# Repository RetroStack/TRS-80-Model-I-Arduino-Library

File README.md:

# TRS-80 Model I Arduino Library

**NOTE**: This library is under active development and breaking changes still happen between major versions. See the [changelog](CHANGELOG.md) for what changed in the current release, including the migration notes for 2.0.0.

Arduino library for interfacing with TRS-80 Model I hardware via the 40-pin edge connector. Control memory, video, keyboard, and bus signals to create ROM dumpers, RAM testers, and custom peripherals.

**Hardware Required:** Arduino Mega 2560 (only board with sufficient GPIO pins)

## Quick Start

### Basic Usage

```cpp
#include <M1Shield.h>
#include <Display_ST7789_320x240.h>  // Choose your display

Display_ST7789_320x240 displayProvider;

void setup() {
    M1Shield.begin(displayProvider);
}

void loop() {
    M1Shield.loop();
}
```

### Read & Write

```cpp
#include <Model1.h>

void setup() {
    Model1.begin();
    Model1.activateTestSignal();

    uint8_t data = Model1.readMemory(0x0000);  // Read ROM
    Model1.writeMemory(0x3C00, 0x41);          // Write to video RAM

    Model1.deactivateTestSignal();
}
```

### UI Framework with String Support

```cpp
#include <ContentScreen.h>

class MyScreen : public ContentScreen {
public:
    MyScreen() {
        // Three ways to set titles/text - choose what fits your needs:
        setTitle("Static Title");                    // Simple C-string
        setTitle(String("Score: ") + String(score)); // Dynamic Arduino String
        setTitleF(F("Memory Efficient"));            // Flash string (F-macro)
    }

protected:
    void _drawContent() override {
        // Draw dynamic content easily
        String playerName = "Alice";
        drawText(10, 10, String("Player: ") + playerName, WHITE);
        drawTextF(10, 30, F("Static text"), YELLOW);  // Saves RAM
    }
};
```

## Key Features

- **Complete TRS-80 Bus Control** - Read/write memory, control signals, interrupts
- **High-Level Classes** - Model1, Video, Keyboard, ROM, Cassette for easy access
- **Low-Level Access** - Model1LowLevel for advanced users requiring precise control
- **M1Shield Support** - Hardware abstraction for Arduino shield with display/input
- **UI Framework** - Screen management system for building interactive applications
- **Flexible String Support** - All text functions support C-strings, Arduino Strings, and F-strings
- **Multiple Display Support** - ST7789, ILI9341, ST7796, SSD1306, and more
- **Arduino Compatible** - Standard Print interface, familiar patterns

## Installation

1. Install via Arduino Library Manager or download from GitHub
2. Connect Arduino Mega 2560 to TRS-80 (M1Shield recommended, direct wiring supported)
3. Try examples: **M1Shield/SimpleM1Shield** or **Model1/Model1/SimpleModel1**

## Examples

**[Complete Examples Guide](examples/)** - Comprehensive examples with progressive learning paths

The examples folder contains 35 examples organized by functionality:

- **[M1Shield Examples](examples/M1Shield/)** - Hardware platform and display examples
- **[Model1 Examples](examples/Model1/)** - TRS-80 hardware interface (ROM, RAM, Video, Keyboard, etc.)
- **[UI Examples](examples/UI/)** - User interface framework and screen management
- **[Logger Examples](examples/Logger/)** - Debugging and monitoring system

All examples follow a Simple/Comprehensive pattern for progressive learning, with complete documentation and integration guidance.

## Connection Options

**M1Shield (Recommended):** Clean, safe connection with built-in display and controls  
**Direct Wiring:** Connect via jumper wires using our [pin mapping guide](docs/PinMapping.md)

**WARNING:** **See [TEST Signal Fix](docs/TESTMod.md)** for hardware reliability improvement

## Documentation

**[Complete Documentation](docs/)** - Detailed API reference and guides

## Main TRS-80 Model 1 Repository

For additional resources related to the TRS-80 Model 1, be sure to check out the [central page for the TRS-80 Model 1](https://www.github.com/RetroStack/TRS-80-Model-I) on [RetroStack](https://www.github.com/RetroStack).

## Support this Project

RetroStack is passionate about exploring and preserving the legacy of older computer systems. My work involves creating detailed documentation and videos to share the knowledge. I am also dedicated to reviving these classic systems by reimplementing them and offering replacement parts at no cost. If you're keen on supporting this unique project, I invite you to visit my [Patreon page](https://www.patreon.com/RetroStack). Your support would be immensely valuable and greatly appreciated!

## License

This project is licensed under the MIT License - see the [LICENSE](LICENSE) file for details.

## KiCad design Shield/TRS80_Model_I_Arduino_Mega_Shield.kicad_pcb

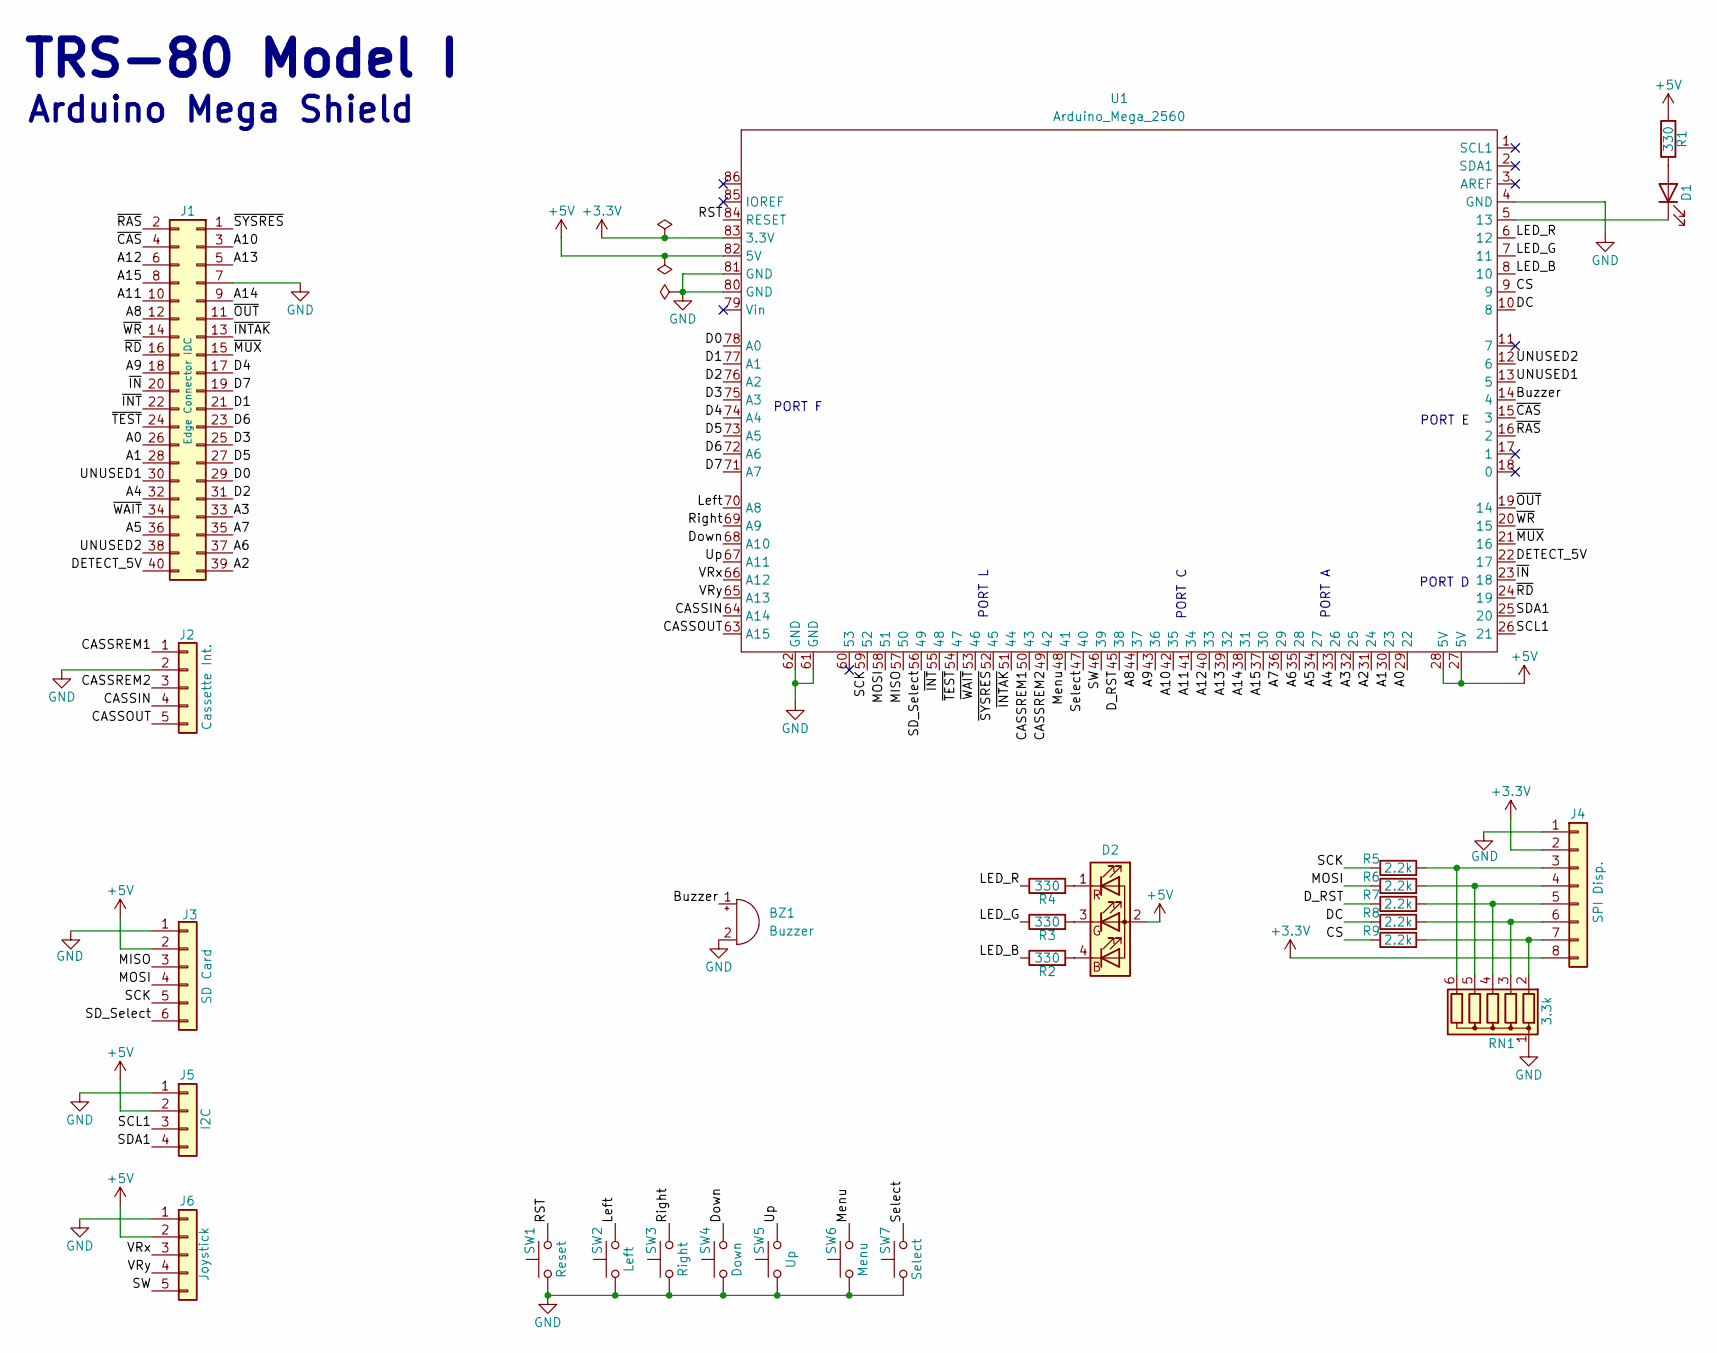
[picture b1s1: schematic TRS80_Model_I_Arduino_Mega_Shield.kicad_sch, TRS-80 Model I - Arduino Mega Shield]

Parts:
BZ1: Buzzer
D1: LED; LED_D3.0mm
D2: LED_ABGR; LED_D5.0mm-4_RGB
J1: Edge Connector IDC; IDC-Header_2x20_P2.54mm_Vertical
J2: Cassette Int.; PinHeader_1x05_P2.54mm_Vertical
J3: SD Card; PinHeader_1x06_P2.54mm_Vertical
J4: SPI Disp.; PinHeader_1x08_P2.54mm_Vertical
J5: I2C; PinHeader_1x04_P2.54mm_Vertical
J6: Joystick; PinHeader_1x05_P2.54mm_Vertical
R1, R2, R3, R4: 330; R_Axial_DIN0207_L6.3mm_D2.5mm_P10.16mm_Horizontal
R5, R6, R7, R8, R9: 2.2k; R_Axial_DIN0207_L6.3mm_D2.5mm_P10.16mm_Horizontal
RN1: 3.3k; R_Array_SIP6
SW1: Reset; SW_SPST_Push
SW2: Left; SW_SPST_Push
SW3: Right; SW_SPST_Push
SW4: Down; SW_SPST_Push
SW5: Up; SW_SPST_Push
SW6: Menu; SW_SPST_Push
SW7: Select; SW_SPST_Push
U1: Arduino_Mega_2560

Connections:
+3.3V: J4.2, J4.8, U1.83 (3.3V)
+5V: D2.2 (A), J3.2, J5.2, J6.2, R1.2, U1.27 (5V), U1.28 (5V), U1.82 (5V)
/A0: J1.26, U1.29 (22)
/A1: J1.28, U1.30 (23)
/A2: J1.39, U1.31 (24)
/A3: J1.33, U1.32 (25)
/A4: J1.32, U1.33 (26)
/A5: J1.36, U1.34 (27)
/A6: J1.37, U1.35 (28)
/A7: J1.35, U1.36 (29)
/A8: J1.12, U1.44 (37)
/A9: J1.18, U1.43 (36)
/A10: J1.3, U1.42 (35)
/A11: J1.10, U1.41 (34)
/A12: J1.6, U1.40 (33)
/A13: J1.5, U1.39 (32)
/A14: J1.9, U1.38 (31)
/A15: J1.8, U1.37 (30)
/Buzzer: BZ1.1 (+), U1.14 (4)
/CASSIN: J2.4, U1.64 (A14)
/CASSOUT: J2.5, U1.63 (A15)
/CASSREM1: J2.1, U1.50 (43)
/CASSREM2: J2.3, U1.49 (42)
/CS: R9.1, U1.9
/D0: J1.29, U1.78 (A0)
/D1: J1.21, U1.77 (A1)
/D2: J1.31, U1.76 (A2)
/D3: J1.25, U1.75 (A3)
/D4: J1.17, U1.74 (A4)
/D5: J1.27, U1.73 (A5)
/D6: J1.23, U1.72 (A6)
/D7: J1.19, U1.71 (A7)
/DC: R8.1, U1.10 (8)
/DETECT_5V: J1.40, U1.22 (17)
/D_RST: R7.1, U1.45 (38)
/Down: SW4.2, U1.68 (A10)
/LED_B: R2.1, U1.8 (10)
/LED_G: R3.1, U1.7 (11)
/LED_R: R4.1, U1.6 (12)
/Left: SW2.2, U1.70 (A8)
/MISO: J3.3, U1.57 (50)
/MOSI: J3.4, R6.1, U1.58 (51)
/Menu: SW6.2, U1.48 (41)
/RST: SW1.2, U1.84 (RESET)
/Right: SW3.2, U1.69 (A9)
/SCK: J3.5, R5.1, U1.59 (52)
/SCL1: J5.3, U1.26 (21)
/SDA1: J5.4, U1.25 (20)
/SD_Select: J3.6, U1.56 (49)
/SW: J6.5, U1.46 (39)
/Select: SW7.2, U1.47 (40)
/Up: SW5.2, U1.67 (A11)
/VRx: J6.3, U1.66 (A12)
/VRy: J6.4, U1.65 (A13)
/~CAS: J1.4, U1.15 (3)
/~INTAK: J1.13, U1.51 (44)
/~INT: J1.22, U1.55 (48)
/~IN: J1.20, U1.23 (18)
/~MUX: J1.15, U1.21 (16)
/~OUT: J1.11, U1.19 (14)
/~RAS: J1.2, U1.16 (2)
/~RD: J1.16, U1.24 (19)
/~SYSRES: J1.1, U1.52 (45)
/~TEST: J1.24, U1.54 (47)
/~WAIT: J1.34, U1.53 (46)
/~WR: J1.14, U1.20 (15)
unnamed: D1.2 (A), R1.1
unnamed: D1.1 (K), U1.5 (13)
unnamed: D2.4 (BK), R2.2
unnamed: D2.3 (GK), R3.2
unnamed: D2.1 (RK), R4.2
unnamed: J4.3, R5.2, RN1.6 (R5)
unnamed: J4.4, R6.2, RN1.5 (R4)
unnamed: J4.5, R7.2, RN1.4 (R3)
unnamed: J4.6, R8.2, RN1.3 (R2)
unnamed: J4.7, R9.2, RN1.2 (R1)

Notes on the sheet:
PORT F
PORT L
TRS-80 Model I
Arduino Mega Shield
PORT D
PORT C
PORT E
PORT A

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
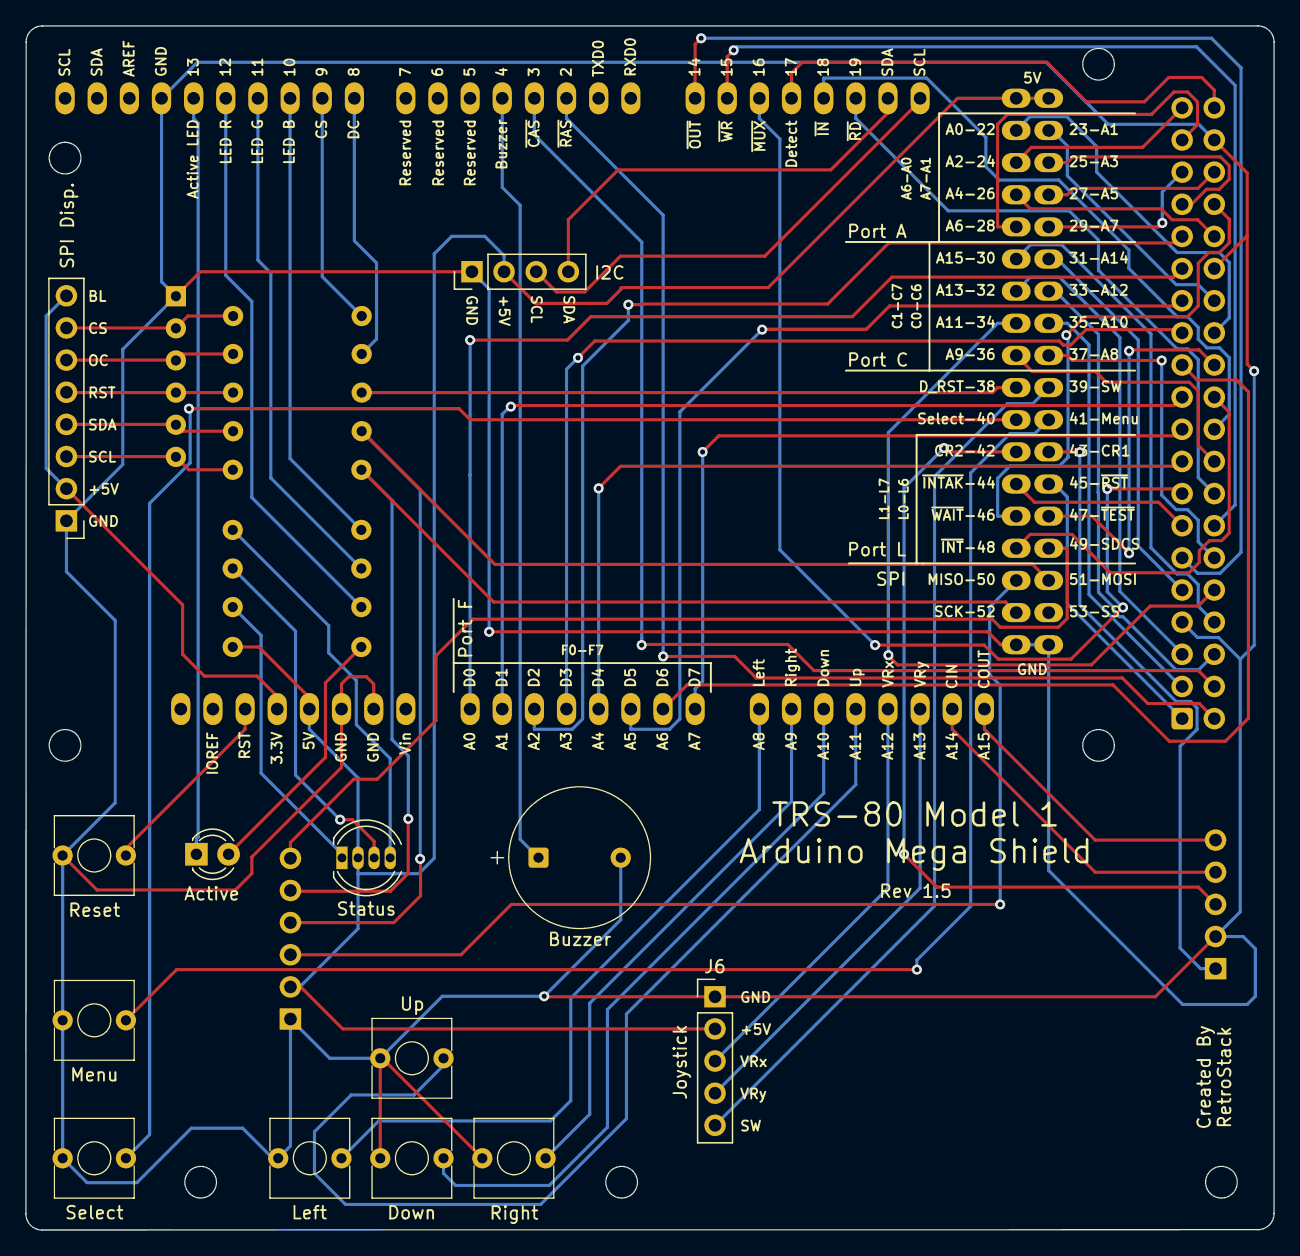
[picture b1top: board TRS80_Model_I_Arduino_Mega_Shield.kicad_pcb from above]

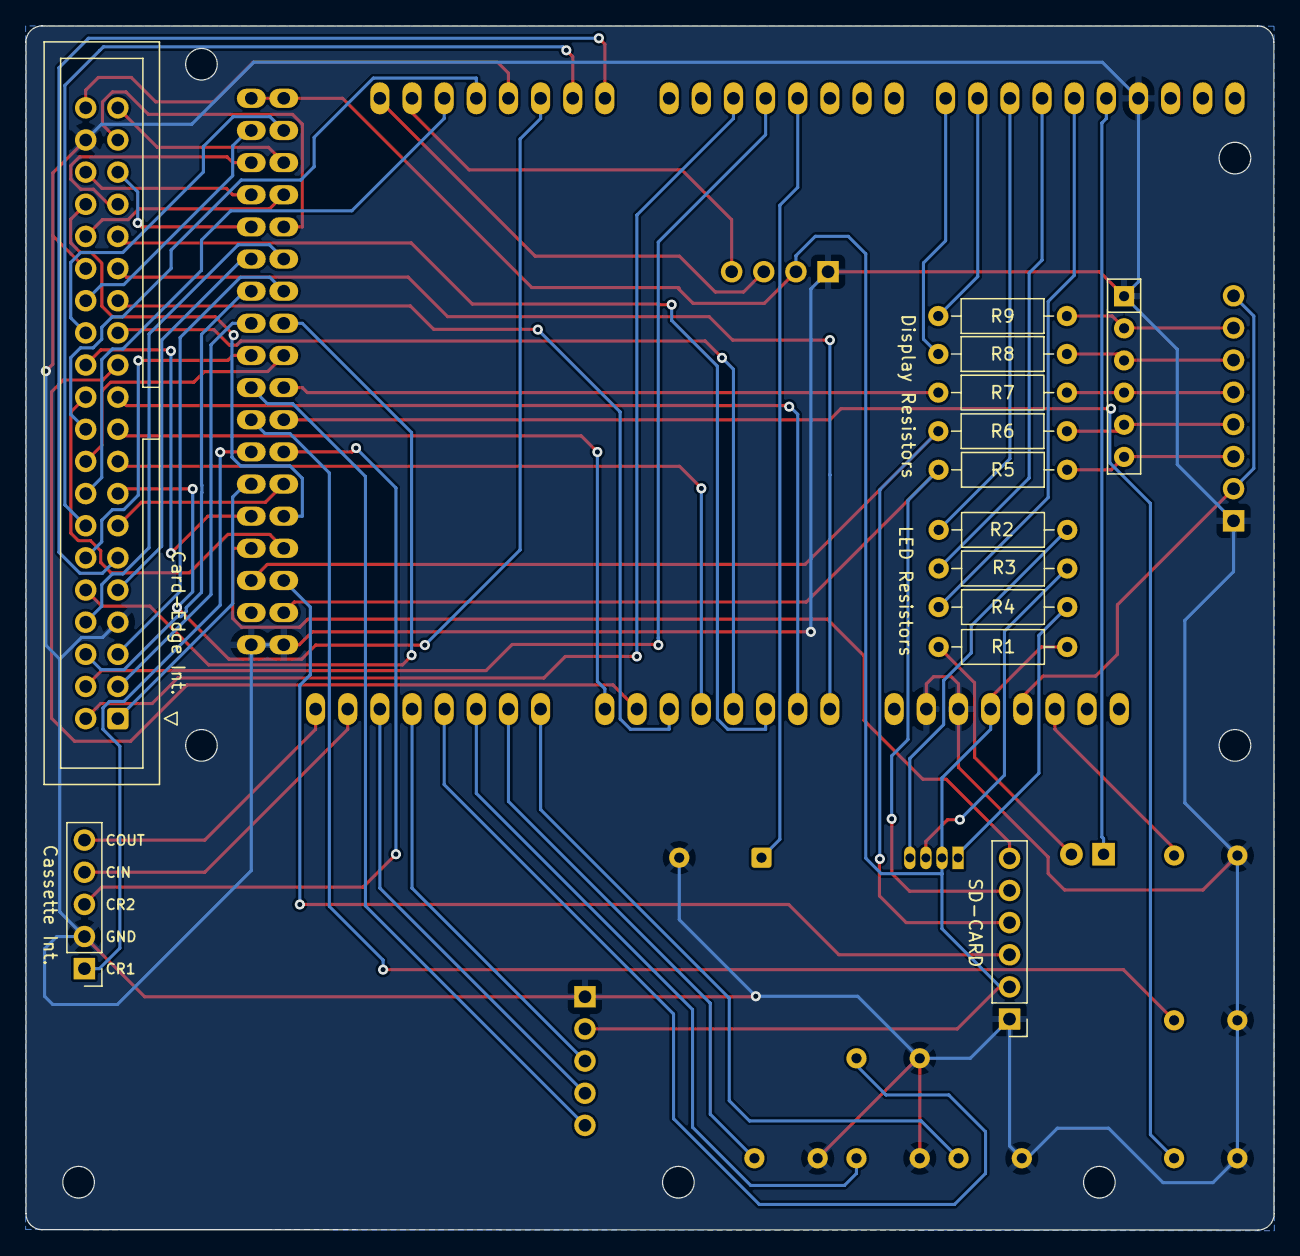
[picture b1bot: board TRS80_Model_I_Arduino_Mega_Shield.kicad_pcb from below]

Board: 2 copper layers, 98.6 x 95.1 mm, 27 parts (13 on the bottom side), 77 nets.

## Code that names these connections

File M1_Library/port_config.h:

#ifndef PORT_CONFIG_H
#define PORT_CONFIG_H

#include <Arduino.h>

// Low- and high-byte port for Address Bus
#define BUS_ADDR_LOW_PORT A
#define BUS_ADDR_HIGH_PORT C

// Byte port for Data Bus
#define BUS_DATA_PORT F

// Port L, Bit(0) 4, Pin 45
const uint8_t PIN_SYS_RES_ON = 0b00000001 << 4;
const uint8_t PIN_SYS_RES_OFF = ~(0b00000001 << 4);
#define PIN_SYS_RES_PORT L

// Port L, Bit(0) 5, Pin 44
const uint8_t PIN_INT_ACK_ON = 0b00000001 << 5;
const uint8_t PIN_INT_ACK_OFF = ~(0b00000001 << 5);
#define PIN_INT_ACK_PORT L

// Port E, Bit(0) 4, Pin 2
const uint8_t PIN_RAS_ON = 0b00000001 << 4;
const uint8_t PIN_RAS_OFF = ~(0b00000001 << 4);
#define PIN_RAS_PORT E

// Port E, Bit(0) 5, Pin 3
const uint8_t PIN_CAS_ON = 0b00000001 << 5;
const uint8_t PIN_CAS_OFF = ~(0b00000001 << 5);
#define PIN_CAS_PORT E

// Port L, Bit(0) 0, Pin 49
const uint8_t PIN_MUX_ON = 0b00000001 << 0;
const uint8_t PIN_MUX_OFF = ~(0b00000001 << 0);
#define PIN_MUX_PORT L

// Port D, Bit(0) 2, Pin 19
const uint8_t PIN_RD_ON = 0b00000001 << 2;
const uint8_t PIN_RD_OFF = ~(0b00000001 << 2);
#define PIN_RD_PORT D
#define PIN_RD 19 // for Interrupt

// Port G, Bit(0) 1, Pin 40
const uint8_t PIN_WR_ON = 0b00000001 << 1;
const uint8_t PIN_WR_OFF = ~(0b00000001 << 1);
#define PIN_WR_PORT G
#define PIN_WR 40 // for Interrupt

// Port D, Bit(0) 3, Pin 18
const uint8_t PIN_IN_ON = 0b00000001 << 3;
const uint8_t PIN_IN_OFF = ~(0b00000001 << 3);
#define PIN_IN_PORT D
#define PIN_IN 18 // for Interrupt

// Port D, Bit(0) 7, Pin 38
const uint8_t PIN_OUT_ON = 0b00000001 << 7;
const uint8_t PIN_OUT_OFF = ~(0b00000001 << 7);
#define PIN_OUT_PORT D
#define PIN_OUT 38 // for Interrupt

// Port L, Bit(0) 1, Pin 48
const uint8_t PIN_INT_ON = 0b00000001 << 1;
const uint8_t PIN_INT_OFF = ~(0b00000001 << 1);
#define PIN_INT_PORT L

// Port L, Bit(0) 2, Pin 47
const uint8_t PIN_TEST_ON = 0b00000001 << 2;
const uint8_t PIN_TEST_OFF = ~(0b00000001 << 2);
#define PIN_TEST_PORT L

// Port L, Bit(0) 3, Pin 46
const uint8_t PIN_WAIT_ON = 0b00000001 << 3;
const uint8_t PIN_WAIT_OFF = ~(0b00000001 << 3);
#define PIN_WAIT_PORT L

#endif // PORT_CONFIG_H

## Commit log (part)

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2024-06-25 Remove missing implementations
2024-08-31 v0.91
2024-09-02 Adding support for PlatformIO/VSCode
2024-09-02 Remove .pio from repo
2024-09-02 Make this work with Arduino IDE
2024-09-02 Move folder up
2024-09-02 Run a formatter over it
2024-09-02 Add logger
2024-09-02 Removal of unused code and other cleanup
2024-09-14 Add signal classes and replace usage
2024-09-16 Add support for Arduino library
2024-09-16 Improve interrupt handling
2024-09-16 Add examples for the library
2024-09-16 Add rudimentary video mode support
2024-09-16 Add cassette support
2024-09-16 Add version number
2024-09-16 Add address space functions
2024-09-16 Add keyboard checks
2024-09-16 Add character conversion
2024-09-16 Improve cassette interface
2024-09-16 Update Arduino keywords
2024-09-17 Fixing general issues in library examples
2024-09-28 Improve documentation
2024-11-07 Fixing various bugs
2024-11-14 Update Cassette.ino
    Fix issue for #8, updating the code with the correct/latest name.
2024-11-25 Remove unnecessary outputs
2025-06-27 Use new[] and delete for memory
2025-06-27 Remove duplicate default arguments
2025-06-27 Fix getContent declaration
2025-06-27 Fix ROM header newline and example
2025-06-27 Fix dynamic array allocation
2025-06-28 Use IO address in writeIO
2025-06-28 Various fixes
2025-07-13 Verified ROM
2025-07-13 Fixes for video
2025-07-13 A few improvements for video
2025-07-13 Allowing raw reads
2025-07-13 Fixes for cassette interface
2025-07-13 Update version
2025-07-13 Update DRAM example
2025-07-14 Fixes for refresh
2025-07-14 Remove data interrupt code
2025-07-14 Version bump
2025-07-15 Wait 4us before and after TEST signal and a few other fixes
2025-07-15 Update tests
2025-07-16 Attribution
2025-07-16 Fix typo
2025-07-16 Add docs
2025-07-16 Update docs
2025-07-16 Update example
2025-07-22 Arduino style initialization
2025-07-23 Fix ROM printing
2025-07-23 Add Print support for video class
2025-07-23 New release for 1.1.0
2025-07-23 Move the x/y coordinates to the front
2025-07-26 Update KeyboardChangeIterator.cpp
    Addressing issue #16
2025-07-27 Bugfixes
2025-07-27 Add one-time execution feature
2025-07-27 Adding M1Shield and Screen features
2025-07-27 Update ConsoleScreen docs and add Print interface
2025-07-27 Document the TEST Mod
2025-07-27 Update note
2025-07-27 Restructure Examples
2025-07-27 Fix issue with row rendering on too short lists
2025-07-27 Bugfixes in menu
2025-07-27 Menu Bugfix for alignment
2025-07-27 Speed up M1TerminalScreen again
2025-07-27 Improve speed
2025-07-27 Add additional support of displays
2025-07-27 Add more screen support
2025-07-27 Bugfix for graphic driver
2025-07-27 Include libs
2025-07-27 Sequencing of headers
2025-07-27 Adding display providers
2025-07-27 Fix example style
2025-07-27 Split examples
2025-07-27 Comprehensive example
2025-07-27 Update M1Shield doc image
2025-07-28 Add joystick activation
2025-07-28 Make sure to only write to the screen when active
2025-07-28 Add composite Logger
2025-07-28 Update logger docs
2025-07-28 Add logger screen
2025-07-28 Update Cassette.cpp
    Missing setLogger()
2025-07-29 Adding more screens
2025-07-29 Fix logger screen
2025-07-29 Cleanup display provider
2025-07-29 Shift to a dataProvider getGFX method
2025-07-29 Give access to the displayProvider from the shield
2025-07-29 Create display feature to displayProvider
2025-07-29 Add display method support
2025-07-29 Convert colors to the display provider
2025-07-29 Add small screen support
2025-07-29 Fix scrolling on small displays
2025-07-29 Fix typos and add missing newlines
2025-07-30 Remove empty file
2025-07-30 Add both modes for SH1106
2025-08-01 Updating the comprehensive demo
2025-08-06 Update CompositeLogger.ino
    replaced Serial.printf with Serial.print/println
2025-08-07 Update Video.cpp
    write() singe byte method, didn't return size
2025-08-07 Update Video.cpp
    read() - fix data type warnings
2025-08-08 Move low-level access to dedicated class
2025-08-08 Add console paging
2025-08-09 Consistent naming
2025-08-14 Change default paging mode
2025-08-14 Make address calculation public
2025-08-14 Add string functions
2025-08-14 Make methods more accessible by moving to public
2025-08-14 Make overwritten functions accessible
2025-08-14 Fix warnings
2025-08-14 Update docsd
2025-08-14 Fix support for display
2025-08-14 Remove M1Terminal class
2025-08-14 Update docs and remove default displayProvider
2025-08-15 Fix FlashString logger
2025-08-15 Support flash functions
2025-08-15 Adds config support with flash strings
2025-08-15 Add drawTextF feature
2025-08-15 Fixing the logger version for F macros
2025-08-15 Add string template functions
2025-08-16 Fix examples
2025-08-16 Add keyName feature
2025-08-16 Fix paging
2025-08-16 Add debug logger
2025-08-16 Fix contentScreen paging issue, adding a new line
2025-08-16 Use more intuitive menu navigation
2025-08-16 Adding getStateData and moving to 1.3.0
2025-08-16 Adding low-level state functions
2025-08-16 Progress bar color change
2025-08-17 Add auto-forward feature
2025-08-17 Fix bug in autoForward
2025-08-17 Add cassette interface to M1Shield
2025-08-17 Enabling pausing for auto-paging
2025-08-17 Shrink size for footer to give more space
2025-08-17 Add notify functionality
2025-08-17 Update changelog
2025-08-17 Consistent color scheme for notify
2025-08-17 Add alert & confirm features
2025-08-17 Only use ASCII
2025-08-17 Adding string versions of various functions to simplify code
2025-08-17 Update documentation
2025-08-17 Provide copilot instructions
2025-08-17 Typo in filename
2025-08-18 Update examples
2025-08-18 Update copilot instructions
2025-08-18 Add headers
2025-08-18 Remove unnecessary comments
2025-08-18 More comment cleanup
2025-08-18 More header cleanup
2025-08-18 Adding more useful logging
2025-08-18 More useful logging of errors
2025-08-19 feat: add title management to screens and update documentation
    - Implemented title management functions in Screen and ContentScreen classes.
    - Updated examples to demonstrate title usage in AnimationDemoScreen, ComprehensiveScreen, InputDemoScreen, LifecycleDemoScreen, and SimpleScreen.
    - Enhanced documentation in ContentScreen.md and Screen.md to reflect new title management features.
    - Cleaned up unused title management code and improved memory handling.
2025-08-19 Refactor logging calls to use errF, warnF, and infoF for better flash memory usage. Update actionTaken method signatures in ContentScreen, MenuScreen, and Screen classes to use int8_t for offset para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
2025-08-20 Refactor and enhance code documentation across multiple files
    - Updated comments for clarity and consistency in ContentScreen.h, DataBus.cpp, DataBus.h, DisplayProvider.h, ILogger.h, Keyboard.cpp, Keyboard.h, KeyboardChangeIterator.h, LoggerScreen.cpp, LoggerSc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
    - Improved method descriptions to better reflect functionality and usage.
    - Added checks and validations in Video::scroll to prevent actions with invalid viewport dimensions.
    - Enhanced joystick and button handling methods in M1Shield for better readability and maintainability.
    - Streamlined memory management functions in Model1 for clarity.
2025-08-20 feat: enhance notification system with customizable background colors
2025-08-22 fix: improve error logging in ContentScreen, MenuScreen, and Screen classes to include current title context
2025-08-22 Add ButtonScreen functionality and related examples
    - Introduced ButtonScreen class for horizontal navigation with footer.
    - Implemented SimpleButton and SelectionDisplay screens for demonstration.
    - Updated existing console and content screens to support new display options.
    - Refactored footer and header methods for better layout management.
    - Enhanced example sketches to showcase new button functionality.
    - Updated library properties and keywords to include ButtonScreen.
2025-08-22 feat: add ButtonScreen documentation for horizontal navigation interface
2025-08-22 feat: add secondary content area support to ContentScreen and related methods
2025-08-22 feat: implement secondary content area support in ContentScreen and related examples
2025-08-22 feat: add rotational logging buffer to LoggerScreen with buffer management methods
2025-08-22 feat: enhance LoggerScreen with dynamic log message management and buffer cleanup
2025-09-19 v1.4.0: FileBrowser, SELECT button, and hardware updates
    Major Features:
    - FileBrowser: Complete SD card file browser with dynamic memory management
    - TextFileViewer & BinaryFileViewer: Full file viewing capabilities
    - SELECT button support across all UI components
    - Hardware pin updates for new M1Shield revision
    - Enhanced buzzer and SD card integration
2025-09-19 Adding isSDCardInserted method
2025-09-23 feat: improve file sorting and add filename path check in FileBrowser
2025-09-23 feat: enhance button navigation in ButtonScreen and MenuScreen; update includes in M1Shield and Model1
2025-09-26 Fix PIN_WR_ON and PIN_WR_OFF definitions
2025-10-12 Adding shield and case
